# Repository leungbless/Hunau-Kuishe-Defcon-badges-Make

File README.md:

# Hunau-Kuishe-Defcon-badges-Make
想自己制作defcon的胸卡，带破解的徽章，或者带游戏的，下载的一些资料，和学习经历和自己的总结，如果做出来，会把原件，代码开源，并且分享制作经历，欢迎大家提交分支，来帮助我们改进我们的第一个徽章。

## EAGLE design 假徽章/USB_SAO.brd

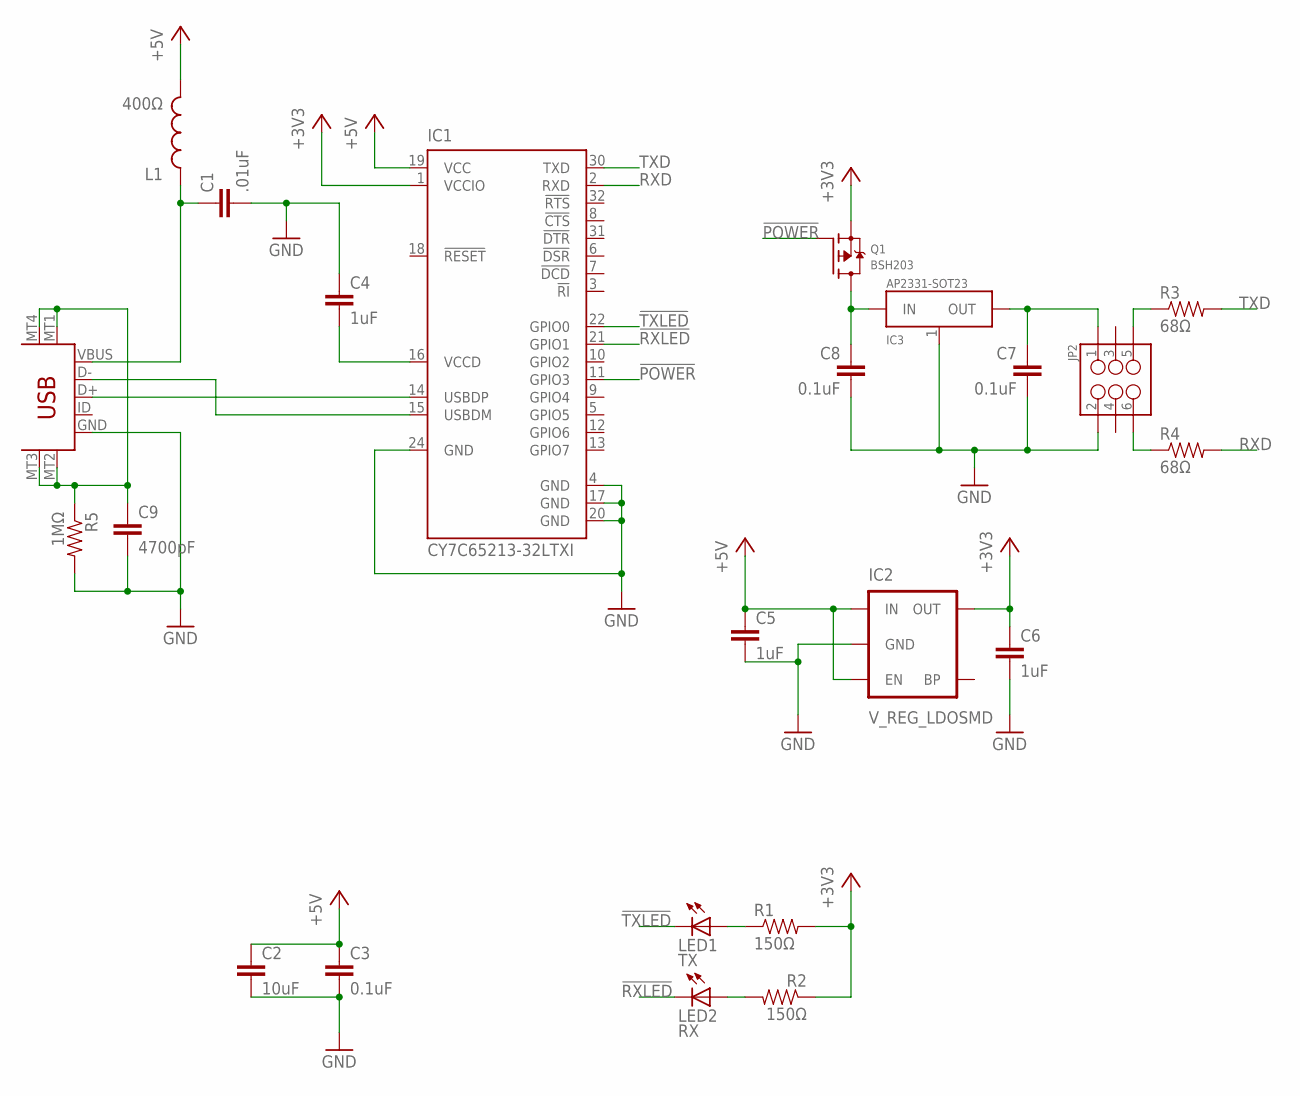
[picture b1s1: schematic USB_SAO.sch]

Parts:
C1: .01uF; 0805
C2: 10uF; 0805
C3, C7, C8: 0.1uF; 0805
C4, C5, C6: 1uF; 0805
C9: 4700pF; 0805
IC1: CY7C65213-32LTXI; QFN32
IC2: V_REG_LDOSMD; SOT23-5
IC3: AP2331-SOT23; SOT23-3
JP1: USB-5PIN-MICROB; USB-MICROB
JP2: M03X2NO_SILK; 2X3-NS
L1: 400Ω; 0805
LED1: TX; CHIP-LED0805
LED2: RX; CHIP-LED0805
Q1: BSH203; SOT23-R
R1, R2: 150Ω; 0805
R3, R4: 68Ω; 0805
R5: 1MΩ; 0805

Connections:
!POWER: IC1.11 (GPIO3), Q1.1 (G)
!RXLED: IC1.21 (GPIO1), LED2.C
!TXLED: IC1.22 (GPIO0), LED1.C
+3V3: C6.1, IC1.1 (VCCIO), IC2.5 (OUT), Q1.2 (S), R1.2, R2.1
+5V: C2.1, C3.1, C5.1, IC1.19 (VCC), IC2.1 (IN), IC2.3 (EN), L1.2
GND: C1.2, C2.2, C3.2, C4.1, C5.2, C6.2, C7.2, C8.2, C9.2, IC1.4 (GND), IC1.17 (GND), IC1.20 (GND), IC1.24 (GND), IC2.2 (GND), IC3.1 (GND), JP1.GND, JP2.2, R5.2
unnamed: IC1.14 (USBDP), JP1.D+
unnamed: IC1.15 (USBDM), JP1.D-
unnamed: LED1.A, R1.1
unnamed: LED2.A, R2.2
unnamed: JP2.5, R3.1
unnamed: C1.1, JP1.VBUS, L1.1
unnamed: JP2.6, R4.1
unnamed: C7.1, IC3.2 (OUT), JP2.1
unnamed: C8.1, IC3.3 (IN), Q1.3 (D)
unnamed: C9.1, JP1.MT1 (MTN1), JP1.MT2 (MTN3), JP1.MT3 (MTN4), JP1.MT4 (MTN2), R5.1
unnamed: C4.2, IC1.16 (VCCD)
RXD: IC1.2 (RXD), R4.2
TXD: IC1.30 (TXD), R3.2

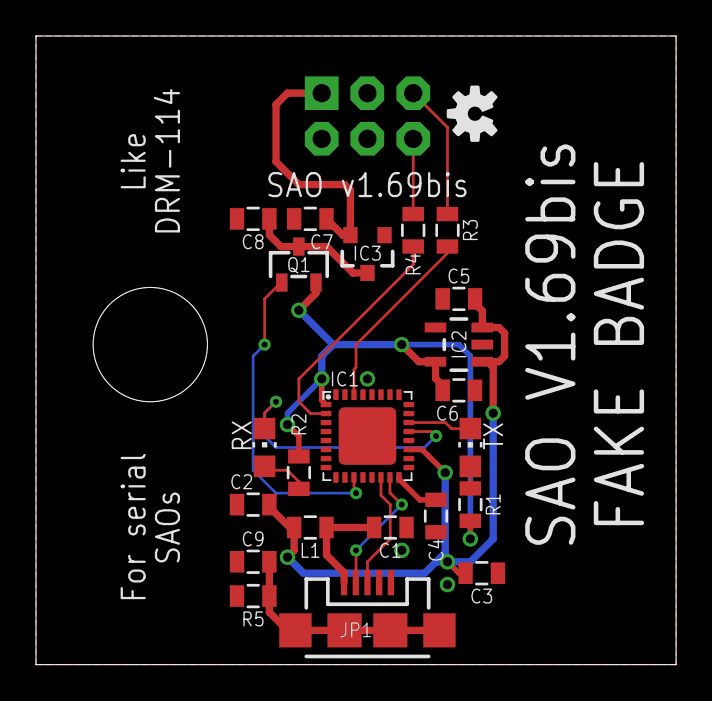
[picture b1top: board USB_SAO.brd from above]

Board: 2 copper layers, 35.6 x 34.9 mm, 24 parts (1 on the bottom side), 19 nets.

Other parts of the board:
U$1: OSHW-LOGO-S

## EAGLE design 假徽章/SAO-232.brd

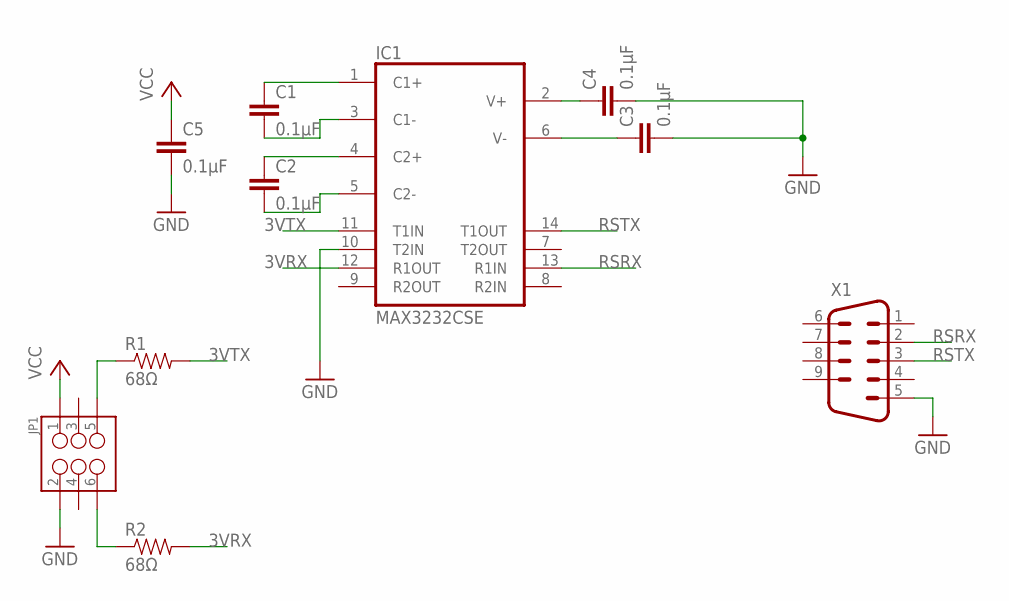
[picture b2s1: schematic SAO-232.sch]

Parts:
C1, C2, C3, C4, C5: 0.1µF; 0805
IC1: MAX3232CSE; SO16
JP1: M03X2NO_SILK; 2X3-NS
R1, R2: 68Ω; 0805
X1: M09D

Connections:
3VRX: IC1.12 (R1OUT), R2.2
3VTX: IC1.11 (T1IN), R1.2
GND: C3.2, C4.2, C5.2, IC1.10 (T2IN), IC1.15 (GND), JP1.2, X1.5
unnamed: C1.1, IC1.1 (C1+)
unnamed: C1.2, IC1.3 (C1-)
unnamed: C2.1, IC1.4 (C2+)
unnamed: C2.2, IC1.5 (C2-)
unnamed: C3.1, IC1.6 (V-)
unnamed: C4.1, IC1.2 (V+)
unnamed: JP1.5, R1.1
unnamed: JP1.6, R2.1
RSRX: IC1.13 (R1IN), X1.2
RSTX: IC1.14 (T1OUT), X1.3
VCC: C5.1, IC1.16 (VCC), JP1.1

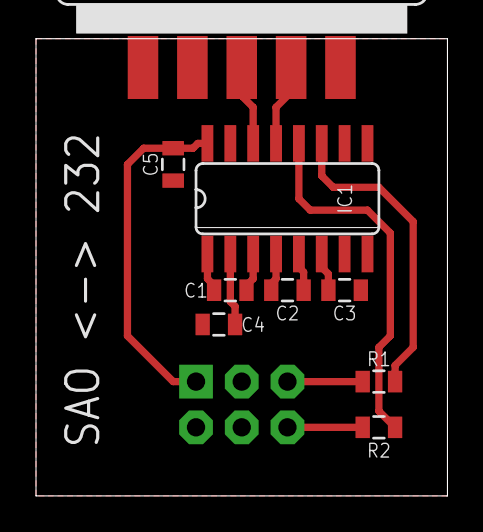
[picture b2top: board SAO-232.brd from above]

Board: 2 copper layers, 22.9 x 25.4 mm, 10 parts (1 on the bottom side), 14 nets.

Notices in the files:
parts and their libraries:
SparkFun-Capacitors: Licensing: CC v3.0 Share-Alike You are welcome to use this library for commercial purposes.
microbuilder: This work is placed in the public domain, and may be freely used for commercial and non-commercial work with the following conditions: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
